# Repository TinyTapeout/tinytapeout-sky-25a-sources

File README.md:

Source repositories for Tiny Tapeout SKY25a projects. Cloned according to the revisions in shuttle_index.json.

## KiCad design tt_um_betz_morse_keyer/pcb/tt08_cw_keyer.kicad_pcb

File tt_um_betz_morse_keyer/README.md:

# Morse Keyer - A lightweight hardware (Verilog) keyer for CW training

- [Read the documentation for project](docs/info.md)

## What is Tiny Tapeout?

Tiny Tapeout is an educational project that aims to make it easier and cheaper than ever to get your digital and analog designs manufactured on a real chip.

To learn more and get started, visit https://tinytapeout.com.

## About this Verilog Project

Please see [docs/info.md](docs/info.md) for a description of this project. An application schematic is shown below.

This design is a CW keyer taking paddle (Iambic) inputs and outputting dits and dahs to a radio/LED/buzzer for training and play. WPM control and Iambic/Straight key selection are done with inputs 7:4 and 0:1, respectively. It also outputs active-high LED controls for a 7-segment display on the board. This design takes advantage of input dip switches and an output seven-segment display present on the demo PCB kit provided with most Tiny Tapeout orders. For more, see: [https://www.tinytapeout.com/specs/pcb/](https://www.tinytapeout.com/specs/pcb/)

If you'd like to use this HDL in your own system, be sure to check the I/O mappings shown in [src/project.v](src/project.v) and adjust accordingly.

The [cocotb](https://docs.cocotb.org/en/stable/index.html) testbench is admittedly sparse. More rigorous testing has been performed with a Spartan 7 FPGA with no noticeable issues.

## Application Schematic for UIO PMOD Port

## Example Breakout PCB Based on Schematic

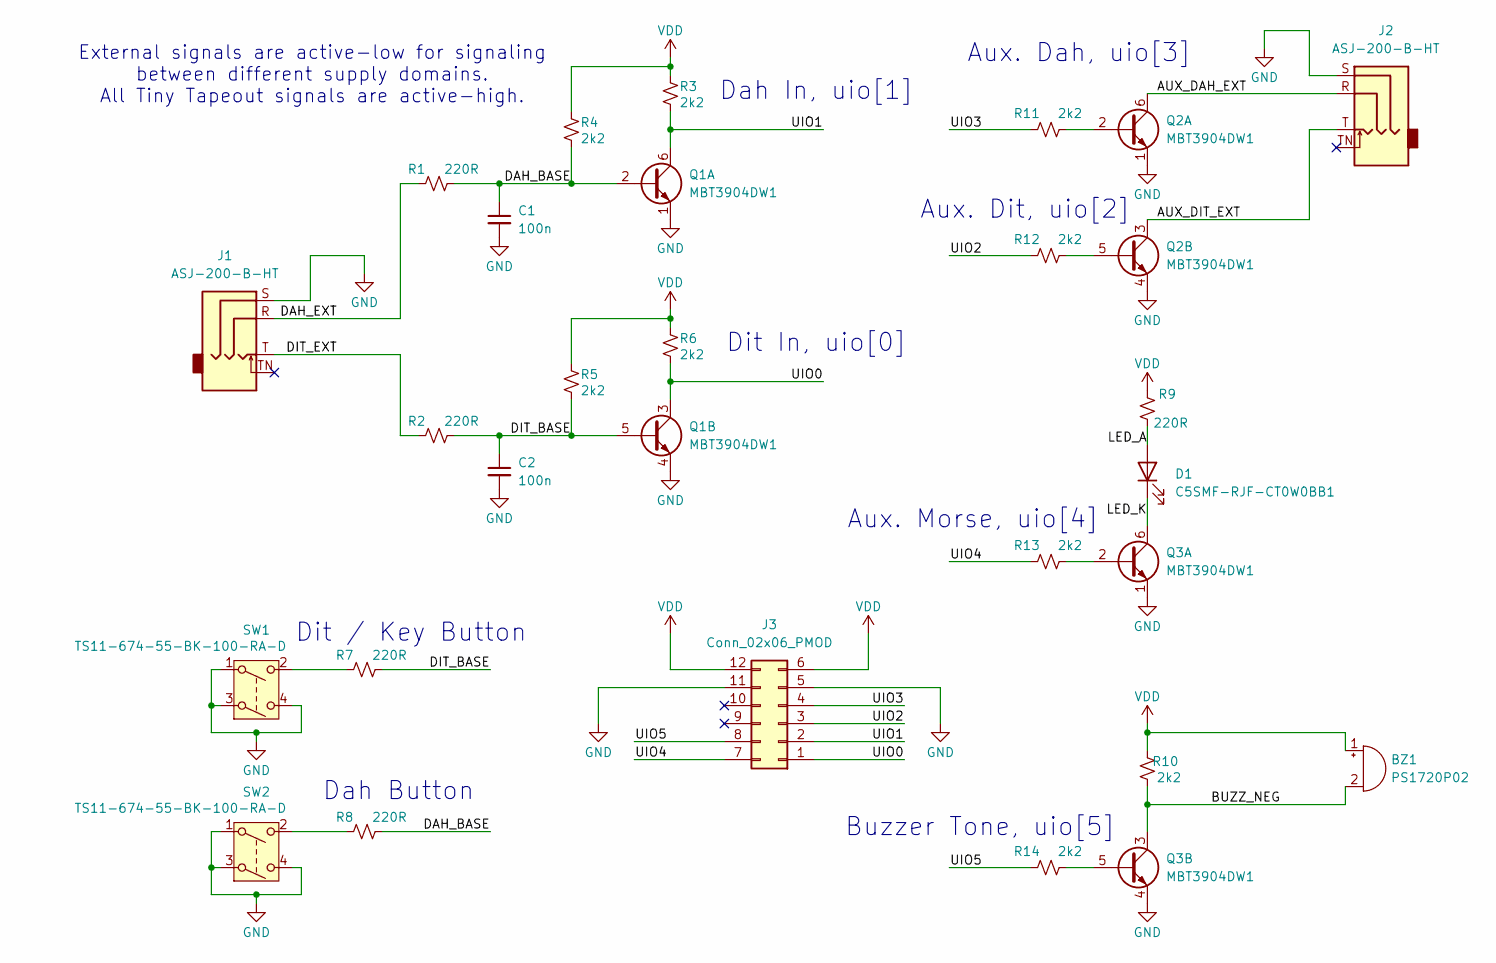
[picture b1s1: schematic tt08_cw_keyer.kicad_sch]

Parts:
BZ1: PS1720P02; Buzzer_TDK_PS1720P02
C1, C2: 100n; C_0805_2012Metric_Pad1.18x1.45mm_HandSolder
D1: C5SMF-RJF-CT0W0BB1; LED_Oval_W5.2mm_H3.8mm
J1, J2: ASJ-200-B-HT
J3: Conn_02x06_PMOD; PinHeader_2x06_P2.54mm_Horizontal_Flipped
Q1, Q2, Q3: MBT3904DW1; SOT-363_SC-70-6
R1, R2, R7, R8, R9: 220R; R_0805_2012Metric_Pad1.20x1.40mm_HandSolder
R3, R4, R5, R6, R10, R11, R12, R13, R14: 2k2; R_0805_2012Metric_Pad1.20x1.40mm_HandSolder
SW1, SW2: TS11-674-55-BK-100-RA-D

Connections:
/AUX_DAH_EXT: J2.R, Q2.6 (C1)
/AUX_DIT_EXT: J2.T, Q2.3 (C2)
/BUZZ_NEG: BZ1.2 (-), Q3.3 (C2), R10.1
/DAH_BASE: C1.1, Q1.2 (B1), R1.2, R4.1, R8.2
/DAH_EXT: J1.R, R1.1
/DIT_BASE: C2.1, Q1.5 (B2), R2.2, R5.1, R7.2
/DIT_EXT: J1.T, R2.1
/LED_A: D1.2 (A), R9.1
/LED_K: D1.1 (K), Q3.6 (C1)
/UIO0: J3.1, Q1.3 (C2), R6.1
/UIO1: J3.2, Q1.6 (C1), R3.1
/UIO2: J3.3, R12.2
/UIO3: J3.4, R11.2
/UIO4: J3.7, R13.2
/UIO5: J3.8, R14.2
GND: C1.2, C2.2, J1.S, J2.S, J3.5, J3.11, Q1.1 (E1), Q1.4 (E2), Q2.1 (E1), Q2.4 (E2), Q3.1 (E1), Q3.4 (E2), SW1.1, SW1.3, SW1.4, SW2.1, SW2.3, SW2.4
unnamed: Q2.2 (B1), R11.1
unnamed: Q2.5 (B2), R12.1
unnamed: Q3.2 (B1), R13.1
unnamed: Q3.5 (B2), R14.1
unnamed: R7.1, SW1.2
unnamed: R8.1, SW2.2
VDD: BZ1.1 (+), J3.6, J3.12, R3.2, R4.2, R5.2, R6.2, R9.2, R10.2

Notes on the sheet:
External signals are active-low for signaling between different supply domains. All Tiny Tapeout signals are active-high.
Dah In, uio[1]
Aux. Dah, uio[3]
Buzzer Tone, uio[5]
Dit In, uio[0]
Dit / Key Button
Aux. Dit, uio[2]
Dah Button
Aux. Morse, uio[4]

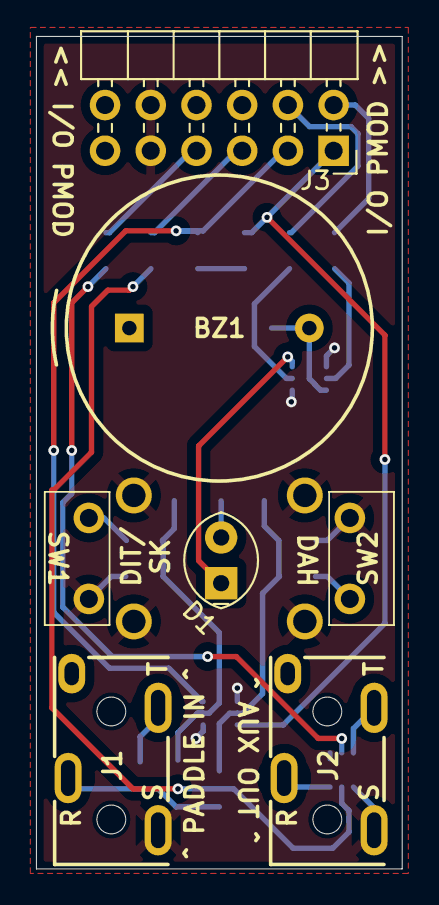
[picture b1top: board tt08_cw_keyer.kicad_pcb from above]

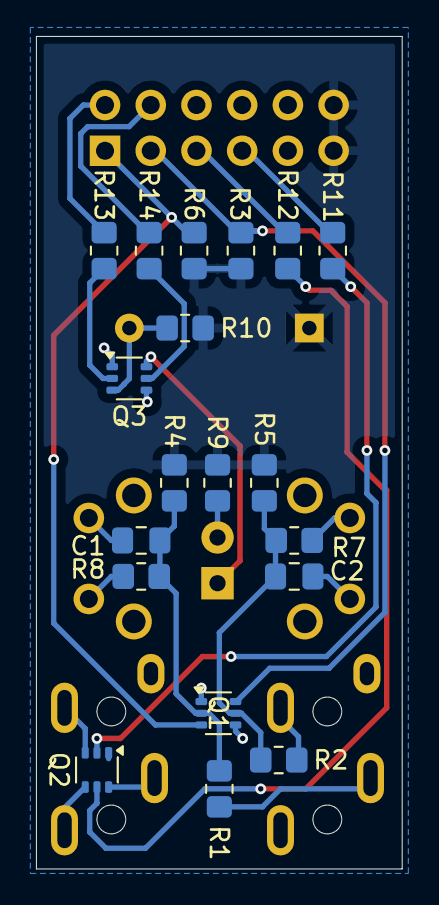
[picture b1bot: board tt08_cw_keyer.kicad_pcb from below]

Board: 2 copper layers, 20.3 x 46.2 mm, 26 parts (19 on the bottom side), 23 nets.

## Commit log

2025-09-23 feat: add shuttle index + scripts
2025-09-23 fix: klayout download URL + precheck command
2025-09-23 feat: add tt_um_factory_test
2025-09-23 feat: add project sources
2025-09-23 chore: skip analog projects
2025-09-24 fix(tt_um_tt_tinyQV): missing .bin files
2025-09-24 fix(tt_um_brandonramos_VGA_Pong_with_NES_Controllers): increase target density
2025-09-24 fix: install sky130_fd_sc_hs std cell library when needed
2025-09-24 fix(tt_um_MichaelBell_hs_mul): install sky130_fd_sc_hs std cell library
